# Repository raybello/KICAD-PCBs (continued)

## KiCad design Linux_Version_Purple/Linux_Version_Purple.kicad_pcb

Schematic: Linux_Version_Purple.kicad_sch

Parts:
C1, C2, C3, C9, C10, C12, C15, C18, C21, C22, C23, C24, C25, C26, C29, C30, C31, C38, C39, C42, C43, C55, C56, C58, C62, C70, C88, C89, C94, C103, C104, C105, C106, C107, C108, C109, C110, C111, C112, C113, C123: 0.22uF; C_0402_1005Metric
C4: 10uF; C_0402_1005Metric
C5, C19, C20, C33, C44, C48, C49, C57, C67, C76, C80, C81, C133, C140: 10uF; C_0603_1608Metric
C6, C8, C13, C34, C36, C45, C47, C50, C54, C65, C68, C69, C71, C72, C75, C77, C78, C82, C84, C85, C90, C114, C119, C122, C125, C126, C129, C130, C134, C135, C139, C141, C143, C145: 0.1uF; C_0402_1005Metric
C7, C32, C37, C40, C53, C83, C102, C128, C132: 22uF; C_0603_1608Metric
C11, C59, C60, C73, C79, C101, C131, C136, C144: 1.0uF; C_0402_1005Metric
C14, C52, C63, C64, C66, C86: 1000pF; C_0402_1005Metric
C16, C27, C87, C91, C93, C98, C115, C120, C138: DNP; C_0402_1005Metric
C17, C28, C92, C95, C96, C97: 18pF; C_0402_1005Metric
C35, C41, C46, C61, C74, C117, C118, C127, C142: 4.7uF; C_0402_1005Metric
C51: 0.022uF; C_0402_1005Metric
C99, C100: 12pF; C_0402_1005Metric
C116, C121: 2.2pF; C_0402_1005Metric
C124: 1uF; C_0603_1608Metric
C137: 47uF; C_0603_1608Metric
D1, D2, D3, D4: RB521S-30; SOD523; LCSC C402277
D5, D6: LED_G_3V; LED_0402_1005Metric
FB1: 120Ω@100MHz; R_0603_1608Metric; LCSC C304464
J1: USB_B_Micro; USB_Micro-B_Amphenol_10118194_Horizontal
J2: Micro_SD_Card; microSD_HC_Wuerth_693072010801
J3: SODIMM-200; SODIMM-BOARD-67.6X50
JP1: BOOT_MODE0; SolderJumper-2_P1.3mm_Open_RoundedPad1.0x1.5mm
JP2: BOOT_MODE1; SolderJumper-2_P1.3mm_Open_RoundedPad1.0x1.5mm
L1, L2, L3: 1uH; L_0603_1608Metric; LCSC C275338
Q1, Q3, Q4, Q5, Q6, Q7: 2SK3018T106; SOT-323_SC-70; LCSC C113315
Q2: RYM002N05T2CL; SOT-723; LCSC Digi-Key Part Number RYM002N05T2CLCT-ND
R1, R2, R8, R9, R11, R12, R14, R16, R20, R25, R32, R33, R34, R42, R73: 0R; R_0402_1005Metric
R3, R15, R22, R52, R62, R63: 10K; C_0402_1005Metric
R4: 215K; R_0402_1005Metric
R5: 147K; R_0402_1005Metric
R6: 1.5M; R_0402_1005Metric
R7, R27, R44: 51R; R_0402_1005Metric
R10, R28, R31, R45, R47, R74, R75, R76, R77, R78, R79, R80, R86, R87, R88, R89, R91, R92, R93, R94, R95, R96, R98, R99, R100, R101, R102, R103, R104, R105, R106, R107, R108, R109: 10K; R_0402_1005Metric
R13, R21, R48, R51, R53, R59, R60, R61: 10R; C_0402_1005Metric
R17, R46: 160K; R_0402_1005Metric
R18, R19, R23, R30, R41: 100K; R_0402_1005Metric
R24: 240R; C_0402_1005Metric
R26: 180K; R_0402_1005Metric
R29: 40.2K; R_0402_1005Metric
R35: 100R; R_0402_1005Metric
R36, R70, R71, R81, R82, R83, R84, R85: 1K; R_0402_1005Metric
R37: 464K; R_0402_1005Metric
R38: 243K; R_0402_1005Metric
R39: 1M; R_0402_1005Metric
R40, R43: 200K; R_0402_1005Metric
R49, R55, R58, R64: DNP; C_0402_1005Metric
R50: 0R; C_0402_1005Metric
R54: 1.5K; C_0402_1005Metric
R56: 1K; C_0402_1005Metric
R57, R66: 240R; R_0402_1005Metric
R65: 2.2M; C_0402_1005Metric
R67: 470R; R_0402_1005Metric
R68, R69: 1.5K; R_0402_1005Metric
R72, R90, R97: DNP; R_0402_1005Metric
SW1: THS102; SW_DIP_SPSTx02_Slide_Copal_CHS-02B_W7.62mm_P1.27mm; LCSC C2758158
SW2: SW_DIP_x04; SW_DIP_SPSTx04_Slide_Copal_CHS-04B_W7.62mm_P1.27mm
TP1: VDD_ARM_SOC_IN; TestPoint_Pad_D1.0mm
TP2: ARM_SOC_PG; TestPoint_Pad_D1.0mm
TP3: VLDO_3V3; TestPoint_Pad_D1.0mm
TP4: VLDO_1V8; TestPoint_Pad_D1.0mm
TP5: DCDC_3V3_PG; TestPoint_Pad_D1.0mm
TP6: NVCC_SD; TestPoint_Pad_D1.0mm
TP7, TP8, TP9, TP10, TP11, TP12: TestPoint_Small; TestPoint_Pad_D1.0mm
TP13: DRAM_PG; TestPoint_Pad_D1.0mm
TP14: ONOFF; TestPoint_Pad_D1.0mm
TP15: DRAM_SDCLK0_P; TestPoint_Pad_D1.0mm
TP16: DRAM_SDCLK0_N; TestPoint_Pad_D1.0mm
TP17: DRAM_ADDR0; TestPoint_Pad_D1.0mm
TP18: DRAM_DATA0; TestPoint_Pad_D1.0mm
TP19, TP25: GND; TestPoint_Pad_D1.0mm
TP20: RST_CP2101; TestPoint_Pad_D1.0mm
TP21: 3V3; TestPoint_Pad_D1.0mm
TP22: UART_RX; TestPoint_Pad_D1.0mm
TP23: QSPIA_DATA0; TestPoint_Pad_D1.0mm
TP24: UART_TX; TestPoint_Pad_D1.0mm
TP26: QSPIA_SCLK; TestPoint_Pad_D1.0mm
U1, U9: MP2159GJ; TSOT-23-8
U2: MCIMX6Y2CVM08AB
U3: RT9169-33GV; SOT-23; LCSC C130830
U4: RT9193-33GB; SOT-23-5; LCSC C15651
U5: MP2144GJ-P; TSOT-23-8; LCSC Digi-Key Part Number 1589-1082-1-ND
U6: MCP1700T-1802E/TT; SOT-23; LCSC C150796
U7: UM805RE; SOT-143; LCSC C620010
U8: UM1750S-00; SOT-23-5; LCSC C620011
U10: UM803RS; SOT-23; LCSC C620009
U11: MT41K256M16TW-107:P; BGA96C80P9X16_1400X800X120; PARTREV P
U12: CP2102-GMR; QFN-28-1EP_5x5mm_P0.5mm_EP3.35x3.35mm; LCSC C6568
U13: SN74LVC2G126DCUR; VSSOP-8_2.4x2.1mm_P0.5mm; LCSC C2652104
U14: USBLC6-2P6; SOT-666; LCSC C2827693
U15: ZB25VQ128ASIG; SOP-8_3.76x4.96mm_P1.27mm; LCSC C609616
Y1: CM7V-T1A-32.768KHZ-12.5PF; Crystal_SMD_3215-2Pin_3.2x1.5mm; LCSC Digi-Key Part Number 2195-CM7V-T1A-32.7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
Y2: 24MHz 10pf; Crystal_SMD_3225-4Pin_3.2x2.5mm; LCSC Digi-Key Part Number 2775-T10GC1-24.000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

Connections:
/ARM_SOC_PG: TP2.1, U1.1 (PG)
/CLK1_N: J3.37, U2.P16 (CCM_CLK1_N)
/CLK1_P: J3.39, U2.P17 (CCM_CLK1_P)
/CSI_DATA0: J3.195, U2.E4 (CSI_DATA00)
/CSI_DATA1: J3.193, U2.E3 (CSI_DATA01)
/CSI_DATA2: J3.194, U2.E2 (CSI_DATA02)
/CSI_DATA3: J3.192, U2.E1 (CSI_DATA03)
/CSI_DATA4: J3.191, U2.D4 (CSI_DATA04)
/CSI_DATA5: J3.190, U2.D3 (CSI_DATA05)
/CSI_DATA6: J3.186, U2.D2 (CSI_DATA06)
/CSI_DATA7: J3.188, U2.D1 (CSI_DATA07)
/CSI_HSYNC: J3.197, U2.F3 (CSI_HSYNC)
/CSI_MCLK: J3.187, U2.F5 (CSI_MCLK)
/CSI_PIXCLK: J3.183, U2.E5 (CSI_PIXCLK)
/CSI_VSYNC: J3.198, U2.F2 (CSI_VSYNC)
/DCDC_3V3: C9.1, C10.1, C59.1, C71.1, C72.1, C123.1, C126.1, C127.1, C128.1, C129.1, C130.1, C131.1, C132.1, J2.4 (VDD), J3.85, J3.87, J3.88, J3.89, J3.90, J3.91, J3.92, J3.93, R1.1, R8.1, R11.1, R14.1, R20.1, R25.2, R34.1, R54.1, R74.1, R75.1, R76.1, R77.1, R80.1, R81.1, R82.1, R83.1, R84.1, R85.1, TP21.1, U2.F13 (NVCC_ENET), U2.H13 (NVCC_UART), U2.J13 (NVCC_GPIO), U6.3 (VI), U13.8 (VCCB), U15.8 (VCC)
/DCDC_3V3_PG: C52.1, C63.1, C64.1, R10.1, R32.2, R34.2, R45.1, TP5.1, U4.3 (EN), U8.3 (~SHDN)
/DISCHG_EN: C14.1, C65.1, C86.1, Q1.2 (G), Q4.2 (G), Q7.2 (G), R31.2
/DRAM_1V35: C20.1, C21.1, C22.1, C23.1, C24.1, C25.1, C26.1, C102.1, C103.1, C104.1, C105.1, C106.1, C107.1, C108.1, C109.1, C110.1, C111.1, C112.1, C113.1, C114.1, C117.1, R42.2, R68.1, U2.G6 (NVCC_DRAM), U2.H6 (NVCC_DRAM), U2.J6 (NVCC_DRAM), U2.K6 (NVCC_DRAM), U2.L6 (NVCC_DRAM), U2.M6 (NVCC_DRAM), U11.A1 (VDDQ), U11.A8 (VDDQ), U11.B2 (VDD), U11.C1 (VDDQ), U11.C9 (VDDQ), U11.D2 (VDDQ), U11.D9 (VDD), U11.E9 (VDDQ), U11.F1 (VDDQ), U11.G7 (VDD), U11.H2 (VDDQ), U11.H9 (VDDQ), U11.K2 (VDD), U11.K8 (VDD), U11.N1 (VDD), U11.N9 (VDD), U11.R1 (VDD), U11.R9 (VDD)
/DRAM_ADDR0: TP17.1, U2.L5 (DRAM_ADDR00), U11.N3 (A0)
/DRAM_ADDR1: U2.H2 (DRAM_ADDR01), U11.P7 (A1)
/DRAM_ADDR2: U2.K1 (DRAM_ADDR02), U11.P3 (A2)
/DRAM_ADDR3: U2.M2 (DRAM_ADDR03), U11.N2 (A3)
/DRAM_ADDR4: U2.K4 (DRAM_ADDR04), U11.P8 (A4)
/DRAM_ADDR5: U2.L1 (DRAM_ADDR05), U11.P2 (A5)
/DRAM_ADDR6: U2.G2 (DRAM_ADDR06), U11.R8 (A6)
/DRAM_ADDR7: U2.H4 (DRAM_ADDR07), U11.R2 (A7)
/DRAM_ADDR8: U2.J4 (DRAM_ADDR08), U11.T8 (A8)
/DRAM_ADDR9: U2.L2 (DRAM_ADDR09), U11.R3 (A9)
/DRAM_ADDR10: U2.M4 (DRAM_ADDR10), U11.L7 (A10/AP)
/DRAM_ADDR11: U2.K3 (DRAM_ADDR11), U11.R7 (A11)
/DRAM_ADDR12: U2.L4 (DRAM_ADDR12), U11.N7 (A12/~BC)
/DRAM_ADDR13: U2.H3 (DRAM_ADDR13), U11.T3 (A13)
/DRAM_ADDR14: U2.G1 (DRAM_ADDR14), U11.T7 (A14)
/DRAM_ADDR15: U2.K5 (DRAM_ADDR15), U11.M7 (NC_M7)
/DRAM_CAS_B: U2.J2 (DRAM_CAS_B), U11.K3 (~CAS)
/DRAM_CS0_B: U2.N2 (DRAM_CS0_B), U11.L2 (~CS)
/DRAM_CS1_B: U2.H5 (DRAM_CS1_B), U11.L1 (NC_L1)
/DRAM_DATA0: TP18.1, U2.T4 (DRAM_DATA00), U11.E3 (DQ0)
/DRAM_DATA1: U2.U6 (DRAM_DATA01), U11.H3 (DQ4)
/DRAM_DATA2: U2.T6 (DRAM_DATA02), U11.H7 (DQ7)
/DRAM_DATA3: U2.U7 (DRAM_DATA03), U11.F8 (DQ3)
/DRAM_DATA4: U2.U8 (DRAM_DATA04), U11.F7 (DQ1)
/DRAM_DATA5: U2.T8 (DRAM_DATA05), U11.H8 (DQ5)
/DRAM_DATA6: U2.T5 (DRAM_DATA06), U11.G2 (DQ6)
/DRAM_DATA7: U2.U4 (DRAM_DATA07), U11.F2 (DQ2)
/DRAM_DATA8: U2.U2 (DRAM_DATA08), U11.D7 (DQ8)
/DRAM_DATA9: U2.U3 (DRAM_DATA09), U11.C3 (DQ9)
/DRAM_DATA10: U2.U5 (DRAM_DATA10), U11.C8 (DQ10)
/DRAM_DATA11: U2.R4 (DRAM_DATA11), U11.C2 (DQ11)
/DRAM_DATA12: U2.P5 (DRAM_DATA12), U11.A7 (DQ12)
/DRAM_DATA13: U2.P3 (DRAM_DATA13), U11.A2 (DQ13)
/DRAM_DATA14: U2.R2 (DRAM_DATA14), U11.B8 (DQ14)
/DRAM_DATA15: U2.R1 (DRAM_DATA15), U11.A3 (DQ15)
/DRAM_DQM0: U2.T7 (DRAM_DQM0), U11.E7 (LDM)
/DRAM_DQM1: U2.T3 (DRAM_DQM1), U11.D3 (UDM)
/DRAM_ODT0: U2.N1 (DRAM_ODT0), U11.K1 (ODT)
/DRAM_ODT1: U2.F1 (DRAM_ODT1), U11.J1 (NC_J1)
/DRAM_PG: TP13.1, U9.1 (PG)
/DRAM_RAS_B: U2.M5 (DRAM_RAS_B), U11.J3 (~RAS)
/DRAM_RESET_B: R3.1, U2.G4 (DRAM_RESET), U11.T2 (~RESET)
/DRAM_SDBA0: U2.M1 (DRAM_SDBA0), U11.M2 (BA0)
/DRAM_SDBA1: U2.H1 (DRAM_SDBA1), U11.N8 (BA1)
/DRAM_SDBA2: U2.K2 (DRAM_SDBA2), U11.M3 (BA2)
/DRAM_SDCKE0: R22.1, U2.M3 (DRAM_SDCKE0), U11.K9 (CKE)
/DRAM_SDCKE1: R15.1, U2.J3 (DRAM_SDCKE1), U11.J9 (NC_J9)
/DRAM_SDCLK0_N: R67.2, TP16.1, U2.P2 (DRAM_SDCLK0_N), U11.K7 (~CK)
/DRAM_SDCLK0_P: R67.1, TP15.1, U2.P1 (DRAM_SDCLK0_P), U11.J7 (CK)
/DRAM_SDQS0_N: C115.2, C116.2, U2.P7 (DRAM_SDQS0_N), U11.G3 (~LDQS)
/DRAM_SDQS0_P: C115.1, C116.1, U2.P6 (DRAM_SDQS0_P), U11.F3 (LDQS)
/DRAM_SDQS1_N: C120.2, C121.2, U2.T2 (DRAM_SDQS1_N), U11.B7 (~UDQS)
/DRAM_SDQS1_P: C120.1, C121.1, U2.T1 (DRAM_SDQS1_P), U11.C7 (UDQS)
/DRAM_SDWE_B: U2.J1 (DRAM_SDWE_B), U11.L3 (~WE)
/DRAM_VREF: C12.1, C88.1, C89.1, C114.2, C122.1, R68.2, R69.1, U2.P4 (DRAM_VREF), U11.H1 (VREFDQ), U11.M8 (VREFCA)
/DRAM_ZQ1: R66.1, U11.L9 (NC_L9)
/ENET1_CRS_DV: J3.101, U2.E16 (ENET1_RX_EN)
/ENET1_RXD0: J3.97, U2.F16 (ENET1_RX_DATA0)
/ENET1_RXD1: J3.99, U2.E17 (ENET1_RX_DATA1)
/ENET1_RXER: J3.126, U2.D15 (ENET1_RX_ER)
/ENET1_TXD0: J3.122, U2.E15 (ENET1_TX_DATA0)
/ENET1_TXD1: J3.124, U2.E14 (ENET1_TX_DATA1)
/ENET1_TXEN: J3.114, U2.F15 (ENET1_TX_EN)
/ENET1_TX_CLK: C28.1, J3.118, R21.2
/ENET2_CRS_DV: J3.117, U2.B17 (ENET2_RX_EN)
/ENET2_RXD0: J3.111, U2.C17 (ENET2_RX_DATA0)
/ENET2_RXD1: J3.113, U2.C16 (ENET2_RX_DATA1)
/ENET2_TXD0: J3.123, U2.A15 (ENET2_TX_DATA0)
/LCD_DATA0: J3.153, R86.1, SW2.1, U2.B9 (LCD_DATA00)
/LCD_DATA1: J3.155, R87.1, U2.A9 (LCD_DATA01)
/LCD_DATA2: J3.164, R88.1, U2.E10 (LCD_DATA02)
/LCD_DATA3: J3.154, R89.1, U2.D10 (LCD_DATA03)
/LCD_DATA4: J3.158, R84.2, R90.1, U2.C10 (LCD_DATA04)
/LCD_DATA5: J3.149, R91.1, SW2.2, U2.B10 (LCD_DATA05)
/LCD_DATA6: J3.151, R92.1, SW2.3, U2.A10 (LCD_DATA06)
/LCD_DATA7: J3.166, R93.1, SW2.4, U2.D11 (LCD_DATA07)
/LCD_DATA8: J3.143, R94.1, U2.B11 (LCD_DATA08)
/LCD_DATA9: J3.145, R95.1, U2.A11 (LCD_DATA09)
/LCD_DATA10: J3.152, R96.1, U2.E12 (LCD_DATA10)
/LCD_DATA11: J3.148, R80.2, R97.1, U2.D12 (LCD_DATA11)
/LCD_DATA12: J3.150, R98.1, U2.C12 (LCD_DATA12)
/LCD_DATA13: J3.139, R99.1, U2.B12 (LCD_DATA13)
/LCD_DATA14: J3.141, R100.1, U2.A12 (LCD_DATA14)
/LCD_DATA15: J3.142, R101.1, U2.D13 (LCD_DATA15)
/LCD_DATA16: J3.144, R102.1, U2.C13 (LCD_DATA16)
/LCD_DATA17: J3.133, R103.1, U2.B13 (LCD_DATA17)
/LCD_DATA18: J3.137, R104.1, U2.A13 (LCD_DATA18)
/LCD_DATA19: J3.138, R105.1, U2.D14 (LCD_DATA19)
/LCD_DATA20: J3.140, R106.1, U2.C14 (LCD_DATA20)
/LCD_DATA21: J3.129, R107.1, U2.B14 (LCD_DATA21)
/LCD_DATA22: J3.131, R108.1, U2.A14 (LCD_DATA22)
/LCD_DATA23: J3.134, R109.1, U2.B16 (LCD_DATA23)
/LCD_DE: J3.163, U2.B8 (LCD_ENABLE)
/LCD_HSYNC: J3.160, U2.D9 (LCD_HSYNC)
/LCD_PCLK: C87.2, J3.161, R48.2
/LCD_RESET: R49.1, R50.1, U2.E9 (LCD_RESET)
/LCD_RST: J3.157, R49.2
/LCD_VSYNC: J3.162, U2.C9 (LCD_VSYNC)
/MX6_POR_B: J3.4, R35.1
/NVCC_CSI: C2.1, C144.1, C145.1, J3.196, R11.2, R12.2, U2.F4 (NVCC_CSI)
/NVCC_LDCIF: C3.1, U2.E13 (NVCC_LCD)
/NVCC_NAND: C1.1, R8.2, R9.2, U2.E7 (NVCC_NAND)
/NVCC_PLL_OUT: C18.1, C19.1, U2.P13 (NVCC_PLL)
/NVCC_SD: C74.1, C75.1, C94.1, R20.2, R37.1, R38.1, R62.2, R63.2, TP6.1, U2.C4 (NVCC_SD1), U8.5 (VOUT)
/ONOFF: J3.14, TP14.1, U2.R8 (ONOFF)
/PMIC_ON_REQ: J3.5, Q5.2 (G), R28.1, U2.T9 (SNVS_PMIC_ON_REQ)
/PMIC_STBY_REQ: J3.3, Q2.2 (G), R18.1, U2.U9 (CCM_PMIC_STBY_REQ)
/POR_B: C91.1, J3.16, R56.2, R58.1, TP12.1, U2.P8 (POR_B)
/RTC_XTALI: C95.2, U2.T11 (RTC_XTALI), Y1.2
/RTC_XTALO: C96.1, U2.U11 (RTC_XTALO), Y1.1
/SD1_CLK: C97.2, J3.179, R61.2
/SD1_CMD: J3.173, R63.1, U2.C2 (SD1_CMD)
/SD1_DATA0: J3.167, R62.1, U2.B3 (SD1_DATA0)
/SD1_DATA1: J3.171, U2.B2 (SD1_DATA1)
/SD1_DATA2: J3.175, U2.B1 (SD1_DATA2)
/SD1_DATA3: J3.169, U2.A2 (SD1_DATA3)
/UART1_RXD: J3.63, R74.2, TP22.1, U2.K16 (UART1_RX_DATA), U13.6 (B2)
/UART1_TXD: J3.57, TP24.1, U2.K14 (UART1_TX_DATA), U13.5 (DIR)
/UART2_RXD: J3.67, U2.J16 (UART2_RX_DATA)
/UART2_TXD: J3.65, U2.J17 (UART2_TX_DATA)
/USB_DBG_DN_CN: U12.5 (D-), U14.6 (I/O1)
/USB_DBG_DP_CN: U12.4 (D+), U14.4 (I/O2)
/USB_OTG1_DN: J3.27, U2.T15 (USB_OTG1_DN)
/USB_OTG1_DP: J3.25, U2.U15 (USB_OTG1_DP)
/USB_OTG1_VBUS: C101.1, C142.1, C143.1, J3.13, U2.T12 (USB_OTG1_VBUS)
/USB_OTG2_DN: J3.21, U2.T13 (USB_OTG2_DN)
/USB_OTG2_DP: J3.19, U2.U13 (USB_OTG2_DP)
/USB_OTG2_VBUS: C11.1, C138.1, C139.1, J3.11, U2.U12 (USB_OTG2_VBUS)
/USB_RXD: R70.1, U12.25 (RXD), U13.3 (A2)
/USB_TXD: R71.1, U12.26 (TXD), U13.2 (A1)
/VDDA_ADC_3P3: C78.1, C79.1, R14.2, R16.2, U2.L13 (VDDA_ADC_3P3), U2.M13 (ADC_VREFH)
/VDDUSB: C67.1, C68.1, U2.R12 (VDD_USB_CAP)
/VDD_ARM_CAP: C37.1, C38.1, C39.1, U2.G9 (VDD_ARM_CAP), U2.G10 (VDD_ARM_CAP), U2.G11 (VDD_ARM_CAP), U2.H11 (VDD_ARM_CAP)
/VDD_ARM_SOC_IN: C40.1, C41.1, C42.1, C43.1, R2.2, U2.H9 (VDD_SOC_IN), U2.H10 (VDD_SOC_IN), U2.J9 (VDD_SOC_IN), U2.J10 (VDD_SOC_IN), U2.K9 (VDD_SOC_IN), U2.K10 (VDD_SOC_IN)
/VDD_COIN_3V: C140.1, C141.1, D3.2 (A), J3.8, R36.1
/VDD_HIGH_CAP: C15.1, C56.1, C57.1, U2.N6 (NVCC_DRAM_2P5), U2.R14 (VDD_HIGH_CAP), U2.R15 (VDD_HIGH_CAP)
/VDD_HIGH_IN: C61.1, C62.1, R1.2, U2.N13 (VDD_HIGH_IN)
/VDD_SNVS_3V3: C35.1, C36.1, C69.1, D2.2 (A), R30.1, U3.1 (OUT), U7.4 (VCC)
/VDD_SNVS_CAP: C58.1, U2.N12 (VDD_SNVS_CAP)
/VDD_SNVS_IN: C70.1, C133.1, C134.1, D2.1 (K), D3.1 (K), J3.6, R36.2, R58.2, R78.2, R79.1, U2.P12 (VDD_SNVS_IN)
/VDD_SOC_CAP: C29.1, C30.1, C31.1, C32.1, U2.G8 (VDD_SOC_CAP), U2.H8 (VDD_SOC_CAP), U2.J8 (VDD_SOC_CAP), U2.J11 (VDD_SOC_CAP), U2.K8 (VDD_SOC_CAP), U2.K11 (VDD_SOC_CAP), U2.L8 (VDD_SOC_CAP), U2.L9 (VDD_SOC_CAP), U2.L10 (VDD_SOC_CAP), U2.L11 (VDD_SOC_CAP)
/VLDO_1V8: C60.1, R9.1, R12.1, TP4.1, U6.2 (VO)
/VLDO_3V3: C46.1, C47.1, R16.1, TP3.1, U4.5 (OUT)
/VSYS: C4.1, C5.1, C6.1, C33.1, C34.1, C48.1, C49.1, C50.1, C76.1, C77.1, C80.1, C81.1, C82.1, C124.1, C125.1, C135.1, C136.1, C137.1, FB1.2, J3.96, J3.98, J3.100, J3.102, J3.104, J3.106, J3.108, J3.110, J3.112, R23.1, U1.2 (VIN), U3.3 (VI), U5.2 (VIN), U8.1 (VIN), U9.2 (VIN), U12.7 (VREGIN), U12.8 (VBUS), U14.5 (VBUS)
/VUSB_UART_3V3: C118.1, C119.1, D5.2 (A), D6.2 (A), U12.6 (VDD)
/XTALI: C99.1, R64.1, R65.1, U2.T16 (XTALI), Y2.3
/XTALO: C100.1, R64.2, U2.T17 (XTALO), Y2.1
/ZQPAD: R24.1, U2.N4 (DRAM_ZQPAD)
/nUSB_OTG_CHD: J3.31, U2.U16 (USB_OTG1_CHD_B)
/nWDOG: C73.1, R50.2
ACC_INT: J3.36, U2.R10 (SNVS_TAMPER0)
AUD_INT: J3.30, U2.P9 (SNVS_TAMPER4)
BLT_PWM: J3.45, U2.N17 (GPIO1_IO08)
BT_DISABLE: J3.32, U2.R9 (SNVS_TAMPER1)
CAN1_RX: J3.80, U2.G14 (UART3_RTS_B)
CAN1_TX: J3.76, U2.H15 (UART3_CTS_B)
CAN2_RX: J3.78, U2.H14 (UART2_RTS_B)
CAN2_TX: J3.72, U2.J15 (UART2_CTS_B)
ECSPI4_MISO: C17.1, J3.105, R13.2
ECSPI4_MOSI: J3.121, U2.B15 (ENET2_TX_EN)
ECSPI4_SCLK: J3.119, U2.A16 (ENET2_TX_DATA1)
ECSPI4_SS0: J3.109, U2.D16 (ENET2_RX_ER)
ENET1_nINT: J3.12, U2.N8 (SNVS_TAMPER5)
ENET2_nINT: J3.42, U2.N11 (SNVS_TAMPER6)
ENET_MDC: J3.53, U2.L16 (GPIO1_IO07)
ENET_MDIO: J3.61, U2.K17 (GPIO1_IO06)
GND: C1.2, C2.2, C3.2, C4.2, C5.2, C6.2, C7.2, C8.2, C9.2, C10.2, C11.2, C12.2, C13.2, C14.2, C15.2, C16.2, C17.2, C18.2, C19.2, C20.2, C21.2, C22.2, C23.2, C24.2, C25.2, C26.2, C27.2, C28.2, C29.2, C30.2, C31.2, C32.2, C33.2, C34.2, C35.2, C36.2, C37.2, C38.2, C39.2, C40.2, C41.2, C42.2, C43.2, C44.2, C45.2, C46.2, C47.2, C48.2, C49.2, C50.2, C51.2, C52.2, C53.2, C54.2, C55.2, C56.2, C57.2, C58.2, C59.2, C60.2, C61.2, C62.2, C63.2, C64.2, C65.2, C66.2, C67.2, C68.2, C69.2, C70.2, C71.2, C72.2, C74.2, C75.2, C76.2, C77.2, C78.2, C79.2, C80.2, C81.2, C82.2, C83.2, C84.2, C85.2, C86.2, C87.1, C88.2, C89.2, C90.1, C91.2, C92.1, C93.1, C94.2, C95.1, C96.2, C97.1, C98.1, C101.2, C102.2, C103.2, C104.2, C105.2, C106.2, C107.2, C108.2, C109.2, C110.2, C111.2, C112.2, C113.2, C117.2, C118.2, C119.2, C122.2, C123.2, C124.2, C125.2, C126.2, C127.2, C128.2, C129.2, C130.2, C131.2, C132.2, C133.2, C134.2, C135.2, C136.2, C137.2, C138.2, C139.2, C140.2, C141.2, C142.2, C143.2, C144.2, C145.2, J1.5 (GND), J1.6 (Shield), J2.6 (VSS), J2.9 (SHIELD), J3.1, J3.2, J3.15, J3.17, J3.20, J3.22, J3.23, J3.26, J3.28, J3.29, J3.35, J3.38, J3.40, J3.41, J3.50, J3.51, J3.59, J3.60, J3.70, J3.71, J3.81, J3.82, J3.84, J3.103, J3.107, J3.115, J3.116, J3.120, J3.125, J3.127, J3.128, J3.130, J3.132, J3.135, J3.136, J3.146, J3.147, J3.156, J3.159, J3.165, J3.168, J3.170, J3.172, J3.174, J3.176, J3.177, J3.178, J3.180, J3.181, J3.182, J3.184, J3.185, J3.189, J3.199, J3.200, Q1.1 (D), Q4.1 (D), Q5.1 (D), Q7.1 (D), R3.2, R15.2, R17.2, R18.2, R19.2, R22.2, R24.2, R29.2, R39.1, R40.2, R41.2, R46.2, R47.2, R52.2, R57.2, R66.2, R69.2, R86.2, R87.2, R88.2, R89.2, R90.2, R91.2, R92.2, R93.2, R94.2, R95.2, R96.2, R97.2, R98.2, R99.2, R100.2, R101.2, R102.2, R103.2, R104.2, R105.2, R106.2, R107.2, R108.2, R109.2, TP19.1, TP25.1, U1.4 (PGND), U1.6 (AGND), U2.A1 (VSS), U2.A17 (VSS), U2.C3 (VSS), U2.C7 (VSS), U2.C11 (VSS), U2.C15 (VSS), U2.E8 (VSS), U2.E11 (VSS), U2.F6 (VSS), U2.F7 (VSS), U2.F8 (VSS), U2.F9 (VSS), U2.F10 (VSS), U2.F11 (VSS), U2.F12 (VSS), U2.G3 (VSS), U2.G5 (VSS), U2.G7 (VSS), U2.G12 (VSS), U2.G15 (VSS), U2.H7 (VSS), U2.H12 (VSS), U2.J5 (VSS), U2.J7 (VSS), U2.J12 (VSS), U2.K7 (VSS), U2.K12 (VSS), U2.L3 (VSS), U2.L7 (VSS), U2.L12 (VSS), U2.M7 (VSS), U2.M8 (VSS), U2.M9 (VSS), U2.M10 (VSS), U2.M11 (VSS), U2.M12 (NGND_KEL0), U2.N3 (VSS), U2.N5 (VSS), U2.N7 (TEST_MODE), U2.R3 (VSS), U2.R5 (VSS), U2.R7 (VSS), U2.R11 (VSS), U2.R16 (VSS), U2.R17 (VSS), U2.T14 (VSS), U2.U1 (VSS), U2.U14 (VSS), U2.U17 (VSS), U3.2 (GND), U4.2 (GND), U5.4 (PGND), U5.6 (AGND), U6.1 (GND), U7.1 (GND), U8.2 (GND), U9.4 (PGND), U9.6 (AGND), U10.1 (GND), U11.A9 (VSS), U11.B1 (VSSQ), U11.B3 (VSS), U11.B9 (VSSQ), U11.D1 (VSSQ), U11.D8 (VSSQ), U11.E1 (VSS), U11.E2 (VSSQ), U11.E8 (VSSQ), U11.F9 (VSSQ), U11.G1 (VSSQ), U11.G8 (VSS), U11.G9 (VSSQ), U11.J2 (VSS), U11.J8 (VSS), U11.M1 (VSS), U11.M9 (VSS), U11.P1 (VSS), U11.P9 (VSS), U11.T1 (VSS), U11.T9 (VSS), U12.3 (GND), U12.29 (GND), U13.4 (GND), U14.2 (GND), U15.4 (GND)
GPIO_DVFS: J3.34, Q3.2 (G), R19.1, U2.P10 (SNVS_TAMPER3)
HDMI_INT: J3.66, U2.K15 (UART1_CTS_B)
I2C1_SCL: J3.75, U2.G17 (UART4_TX_DATA)
I2C1_SDA: J3.77, U2.G16 (UART4_RX_DATA)
I2C2_SCL: J3.79, U2.F17 (UART5_TX_DATA)
I2C2_SDA: J3.68, U2.G13 (UART5_RX_DATA)
LCD_DISP: J3.10, U2.R6 (SNVS_TAMPER9)
unnamed: C7.1, C8.1, L1.2, R2.1, R4.1, R5.1, R6.1, R7.1, TP1.1, U1.5 (OUT)
unnamed: C13.1, R10.2, U1.8 (EN)
unnamed: C16.1, R13.1, U2.D17 (ENET2_TX_CLK)
unnamed: C27.1, R21.1, U2.F14 (ENET1_TX_CLK)
unnamed: C44.1, C45.1, U4.1 (IN)
unnamed: C51.1, U4.4 (BP)
unnamed: C53.1, C54.1, L2.2, R25.1, R26.1, R27.1, U5.5 (OUT)
unnamed: C55.1, R23.2, R28.2, R33.2, U5.8 (EN), U7.2 (~RESET)
unnamed: C66.1, D1.2 (A), R35.2
unnamed: C73.2, D4.2 (A), R39.2
unnamed: C83.1, C84.1, L3.2, R42.1, R43.1, R44.1, U9.5 (OUT)
unnamed: C85.1, R45.2, U9.8 (EN)
unnamed: C90.2, R54.2, R55.1, U10.3 (VCC)
unnamed: C93.2, R59.2, U2.D8 (NAND_RE_B)
unnamed: C98.2, R61.1, U2.C1 (SD1_CLK)
unnamed: C99.2, C100.2, R65.2, Y2.2, Y2.4
unnamed: D1.1 (K), D4.1 (K), R33.1, U7.3 (~MR)
unnamed: D5.1 (K), R70.2
unnamed: D6.1 (K), R71.2
unnamed: FB1.1, J1.1 (VBUS)
unnamed: J1.2 (D-), U14.1 (I/O1)
unnamed: J1.3 (D+), U14.3 (I/O2)
unnamed: JP1.2 (B), R78.1, SW1.4
unnamed: JP2.2 (B), R79.2, SW1.3
unnamed: L1.1, U1.3 (SW)
unnamed: L2.1, U5.3 (SW)
unnamed: L3.1, U9.3 (SW)
unnamed: Q1.3 (S), R7.2
unnamed: Q2.1 (D), Q3.1 (D), R4.2, R17.1, U1.7 (FB)
unnamed: Q2.3 (S), R5.2
unnamed: Q3.3 (S), R6.2
unnamed: Q4.3 (S), R27.2
unnamed: Q5.3 (S), R30.2, R31.1
unnamed: Q6.1 (D), R37.2, R40.1, U8.4 (BYP)
unnamed: Q6.3 (S), R38.2
unnamed: Q7.3 (S), R44.2
unnamed: R26.2, R29.1, U5.7 (FB)
unnamed: R32.1, U5.1 (PG)
unnamed: R43.2, R46.1, U9.7 (FB)
unnamed: R48.1, U2.A8 (LCD_CLK)
unnamed: R51.2, U2.B4 (NAND_ALE)
unnamed: R53.2, U2.C8 (NAND_WE_B)
unnamed: R55.2, R56.1, U10.2 (~RESET)
unnamed: R57.1, U11.L8 (ZQ)
unnamed: R60.2, U2.E6 (NAND_DQS)
unnamed: R72.1, U12.12 (SUSPEND)
unnamed: R72.2, R73.2, U13.1 (VCCA), U13.7 (B1)
unnamed: R73.1, U12.11 (~SUSPEND)
unnamed: R81.2, SW2.5
unnamed: R82.2, SW2.6
unnamed: R83.2, SW2.7
unnamed: R85.2, SW2.8
unnamed: TP20.1, U12.9 (~RST)
PERI_PWREN: J3.44, U2.P11
QSPIA_DATA0: TP23.1, U2.A3 (NAND_READY_B), U15.5 (SI/IO0)
QSPIA_DATA1: U2.C5 (NAND_CE0_B), U15.2 (SO/IO1)
QSPIA_DATA2: U2.B5 (NAND_CE1_B), U15.3 (~WP/IO2)
QSPIA_DATA3: U2.A4 (NAND_CLE), U15.7 (~HOLD/IO3)
QSPIA_SCLK: TP26.1, U2.D5 (NAND_WP_B), U15.6 (SCK)
QSPIA_nSS0: R60.1, R77.2, U15.1 (~CS)
SAI2_BCLK: J3.43, TP8.1, U2.N16 (JTAG_TDI)
SAI2_MCLK: J3.46, TP9.1, U2.P14 (JTAG_TMS)
SAI2_RXD: J3.54, R47.1, TP10.1, U2.M14 (JTAG_TCK)
SAI2_SYNC: J3.52, TP11.1, U2.N15 (JTAG_TDO)
SAI2_TXD: J3.48, TP7.1, U2.N14 (JTAG_TRST_B)
SD1_CD: J3.74, U2.J14 (UART1_RTS_B)
SD1_VSELECT: J3.49, Q6.2 (G), R41.1, U2.M17 (GPIO1_IO05)
SD1_nRST: J3.56, U2.M15 (GPIO1_IO09)
SD2_CLK: C92.2, J2.5 (CLK), R59.1
SD2_CMD: J2.3 (CMD), R53.1, R75.2
SD2_DATA0: J2.7 (DAT0), R76.2, U2.D7 (NAND_DATA00)
SD2_DATA1: J2.8 (DAT1), U2.B7 (NAND_DATA01)
SD2_DATA2: J2.1 (DAT2), U2.A7 (NAND_DATA02)
SD2_DATA3: J2.2 (DAT3/CD), U2.D6 (NAND_DATA03)
SD2_DATA4: U2.C6 (NAND_DATA04)
SD2_DATA5: U2.B6 (NAND_DATA05)
SD2_DATA6: U2.A6 (NAND_DATA06)
SD2_DATA7: U2.A5 (NAND_DATA07)
SD2_nRST: R51.1
SHIFT_SDI: J3.9, JP1.1 (A), SW1.1, U2.T10 (BOOT_MODE0)
SHIFT_SHCP: J3.7, JP2.1 (A), SW1.2, U2.U10 (BOOT_MODE1)
SHIFT_STCP: J3.24, U2.N10 (SNVS_TAMPER7)
SHIFT_nOE: J3.18, U2.N9 (SNVS_TAMPER8)
SPDIF_TX: J3.33, R52.1, U2.P15 (JTAG_MOD)
UART2_CTS_BB: J3.69, U2.H17 (UART3_TX_DATA)
UART2_RTS_BB: J3.73, U2.H16 (UART3_RX_DATA)
USB_OTG1_ID: J3.64, U2.K13 (GPIO1_IO00)
USB_OTG1_OC: J3.62, U2.L15 (GPIO1_IO01)
USB_OTG1_PWR: J3.47, U2.M16 (GPIO1_IO04)
USB_OTG2_OC: J3.55, U2.L17 (GPIO1_IO03)
USB_OTG2_PWR: J3.58, U2.L14 (GPIO1_IO02)

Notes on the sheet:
DDR3/LvDDR3
BT_CFG2[2]
LvDDR3
Vfb=0.6V
Note: 1K/1.5K are OK
R1/R2 = 0.75/0.6
Option #3
Important: GPIO_DVFS / PMIC_STBY_REQ should be PULL DN when system reboot to ensure the VDD_ARM_SOC_IN voltage is not effected by DVFS
UART-USB DEBUG
PU (100K)
Vfb=1V
BT_CFG2[7]
1.8V/3.3V Default: 3.3V
ADC High PSRR
PG pin is pulled up to VIN by the internal resistor 500K OHM
PD (100K)
1.8V/250mA
BT_CFG2[6]
2.5V to 6V
CLK Termination
BT_CFG1[3]
BT_CFG1[1]
BT_CFG2[3]
Current 1A I_Quiescent : 17¦ÌA
PU (47K)
VDDHIGH / NVCC_xxx
BT_CFG1[7]
Note: CLK termination: Place R69 close to U12.
iMX6ULL CPU
BT_CFG1[4]
BT_CFG2[0]
JTAG Debug
R1/R2 = (Vo-Vfb)/Vfb FB = 0.8V 1.8V: R1/R2 = 1/0.8 : 200K/160K 3.3V: R1/R2 = 2.5/0.8 : 500K/160K FB = 1.0V 1.8V: R1/R2 = 0.8/ 1: 160K/200K 3.3V: R1/R2 = 2.3/1 : 464K/200K
3.3V/100mA
POWER
Option #2
BOOT CFG
Check Load capacitance
SD/QSPI
NVCC_GPIO (J13) and NVCC_UART (H13) should share one 0.22uF de-coupling cap. There is no PCB space to fit two caps.

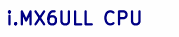
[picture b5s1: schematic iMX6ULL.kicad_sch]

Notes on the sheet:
i.MX6ULL CPU

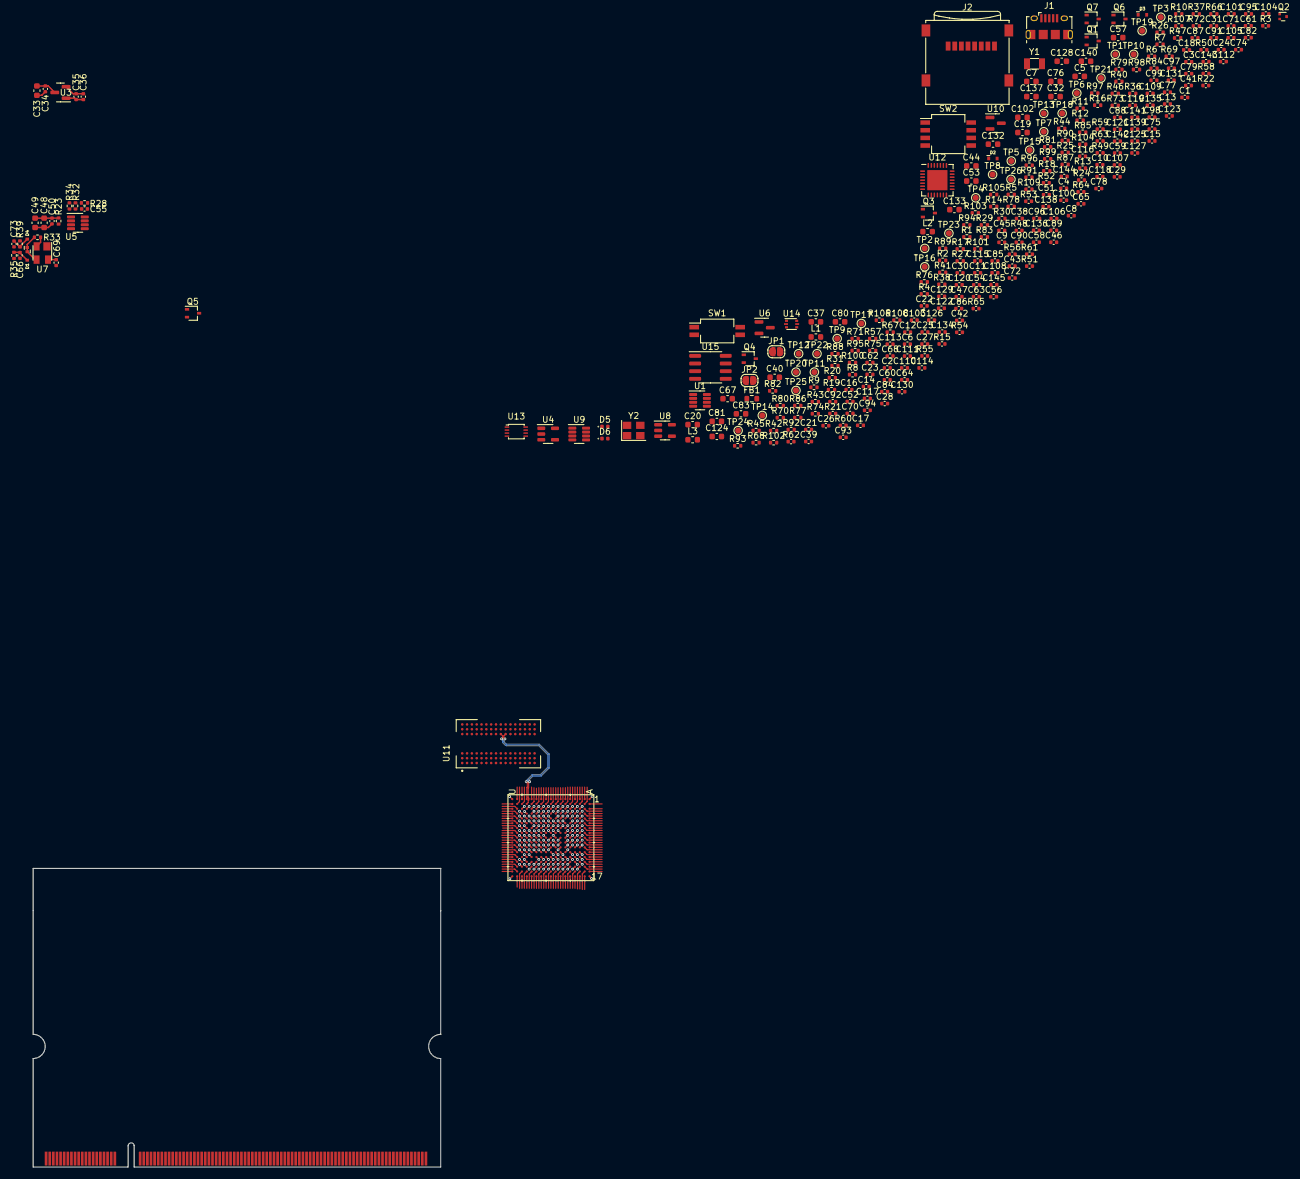
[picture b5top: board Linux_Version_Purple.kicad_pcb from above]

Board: 4 copper layers, 67.6 x 49.5 mm, 321 parts (0 on the bottom side), 279 nets.
